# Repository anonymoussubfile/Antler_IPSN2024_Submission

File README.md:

# Antler_IPSN2024_Submission

We upload all our source code and files for reviewer's reference, including hardware design files, algorithm related files, data collection and model inference related projects on Arduino and MSP, our self-collected datasets, and etc.

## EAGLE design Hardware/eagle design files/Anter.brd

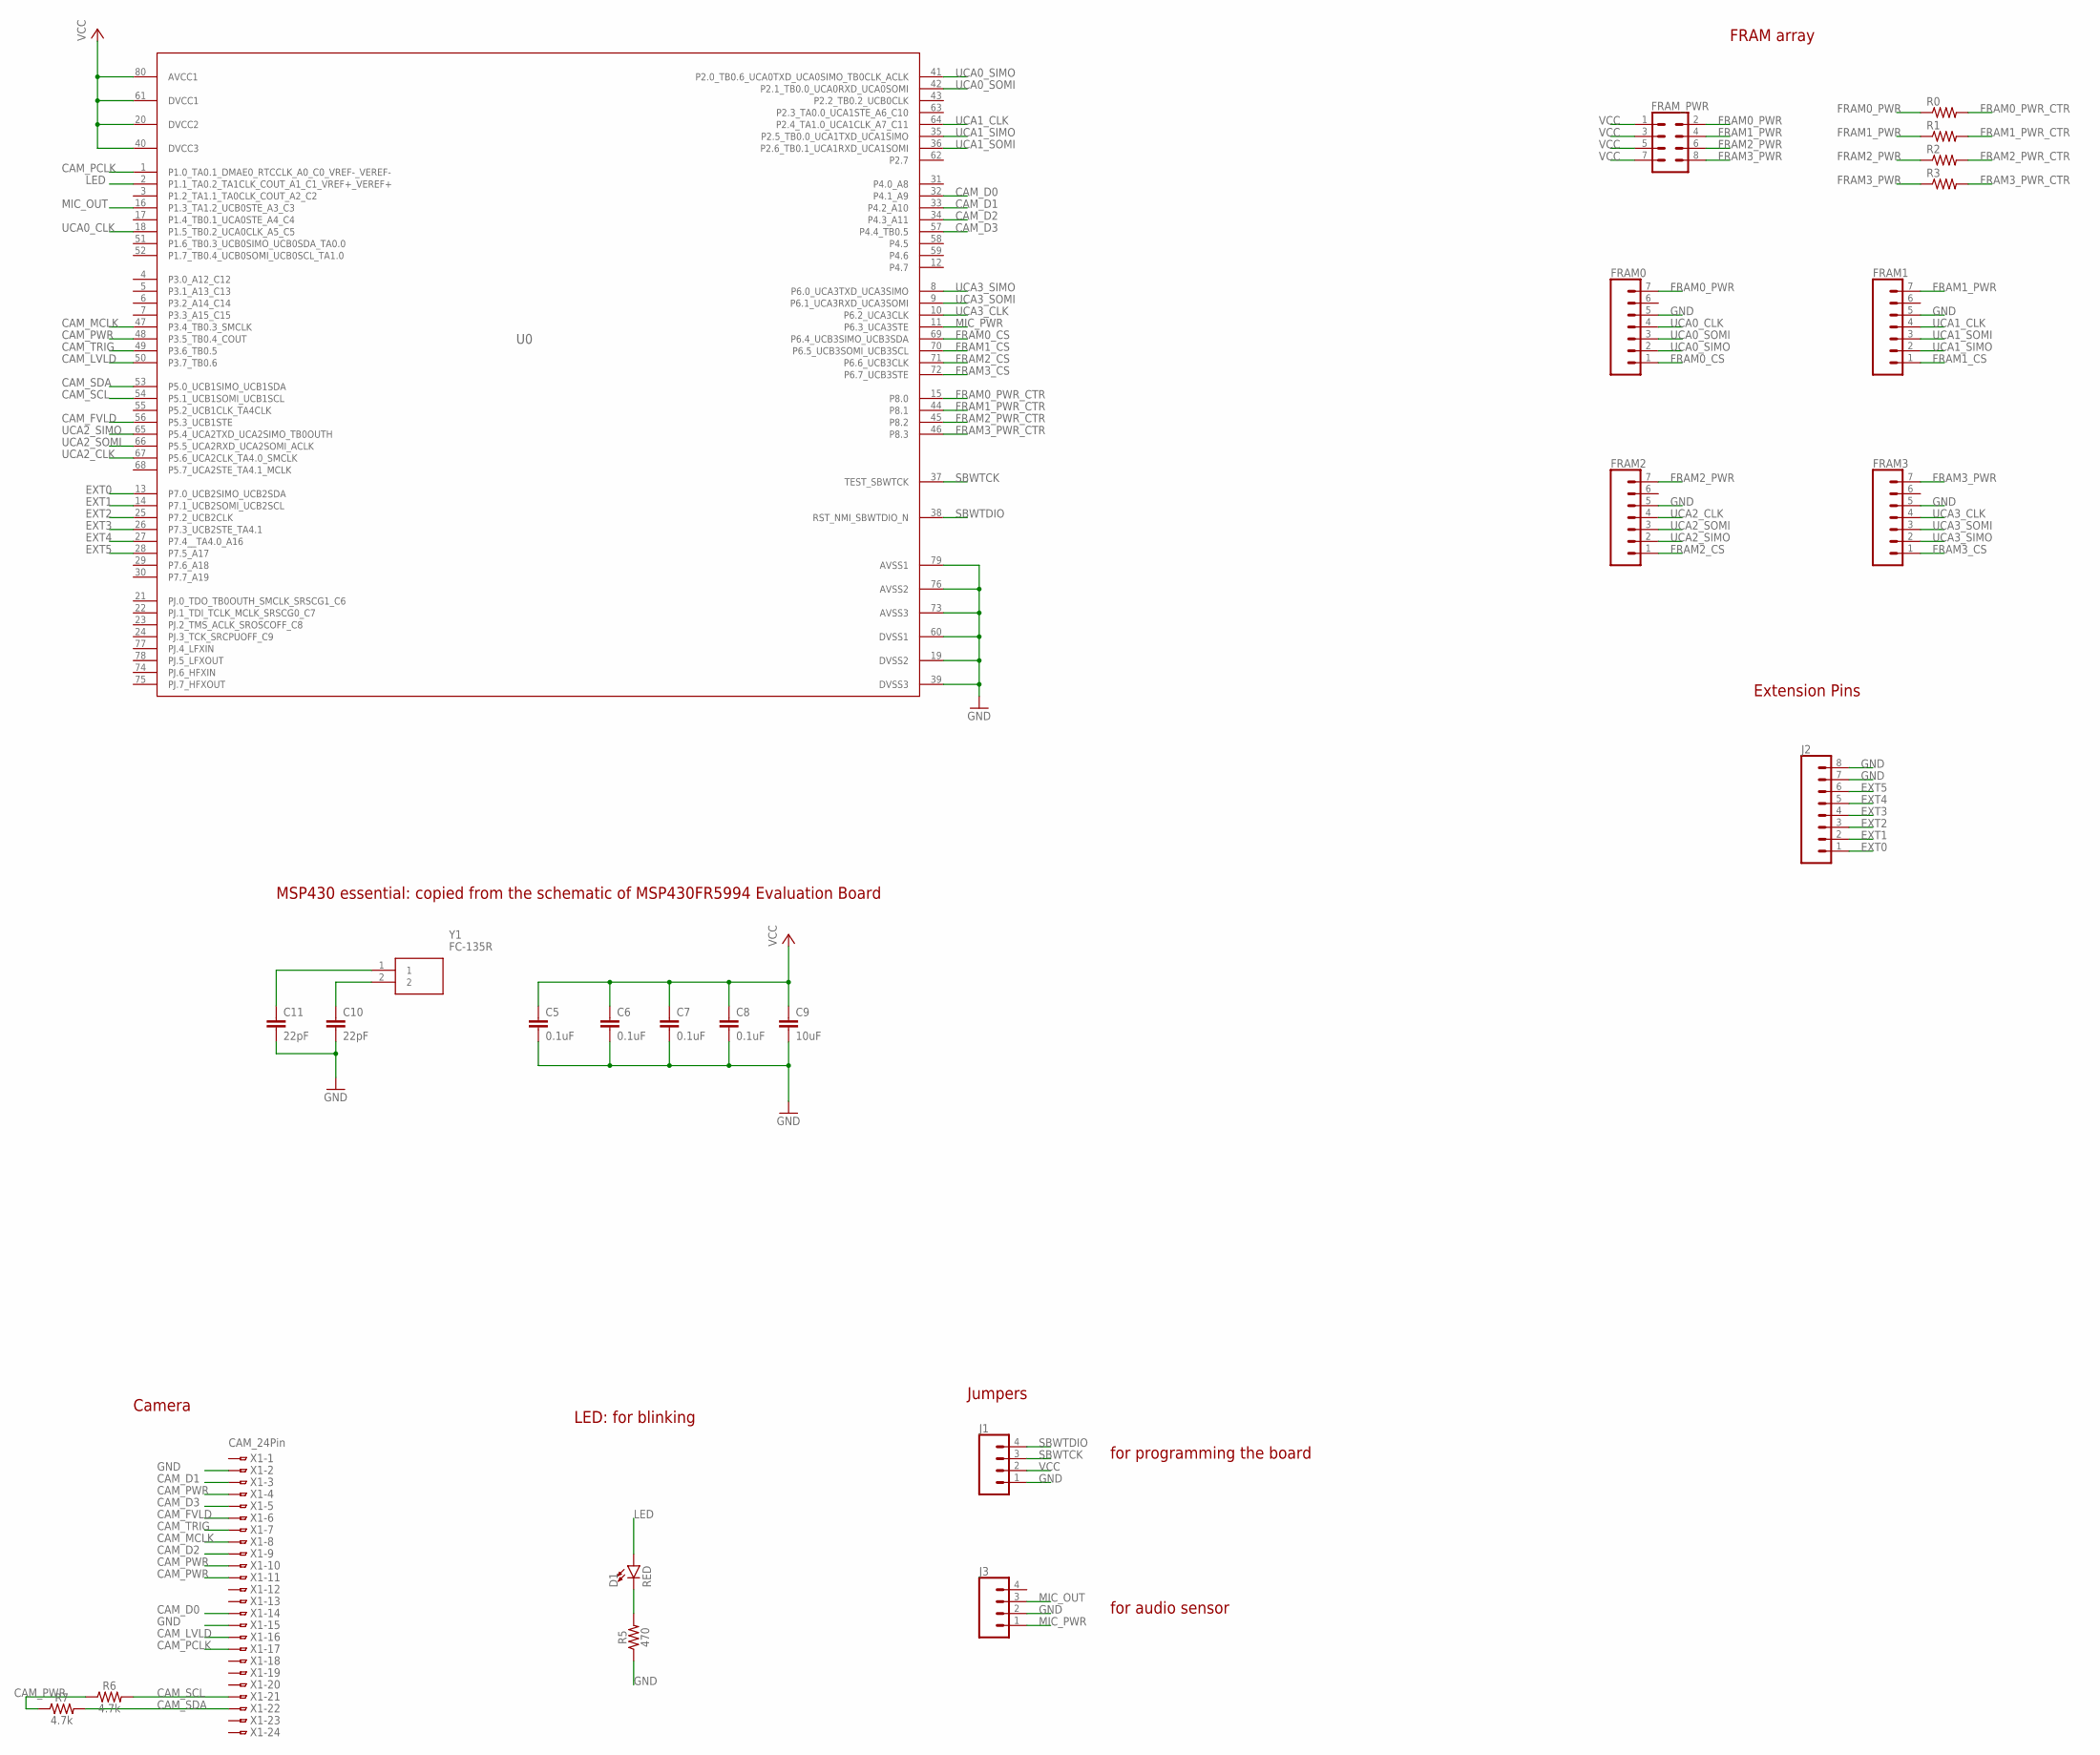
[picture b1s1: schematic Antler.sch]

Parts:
C5, C6, C7, C8: 0.1uF; 0603
C9: 10uF; 0603
C10, C11: 22pF; 0603
D1: RED; LED-0603
FRAM0, FRAM1, FRAM2, FRAM3: CONN_07LOCK; 1X07_LOCK
FRAM_PWR: CONN_04X2; 2X4
J1, J3: CONN_04LOCK; 1X04_LOCK
J2: CONN_08LOCK; 1X08_LOCK
R0, R1, R2, R3: R-US_R0603; R0603
R5: 470; 0603
R6, R7: 4.7k; 0603
U0: MSP430FR5994PN; PN0080A_N
X1: CAM_24Pin; FH12-24S-0.5SH
Y1: FC-135R; FC135327680KAAG0

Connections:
CAM_D0: U0.32 (P4.1_A9), X1.14
CAM_D1: U0.33 (P4.2_A10), X1.3
CAM_D2: U0.34 (P4.3_A11), X1.9
CAM_D3: U0.57 (P4.4_TB0.5), X1.5
CAM_FVLD: U0.56 (P5.3_UCB1STE), X1.6
CAM_LVLD: U0.50 (P3.7_TB0.6), X1.16
CAM_MCLK: U0.47 (P3.4_TB0.3_SMCLK), X1.8
CAM_PCLK: U0.1 (P1.0_TA0.1_DMAE0_RTCCLK_A0_C0_VREF-_VER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), X1.17
CAM_PWR: R6.1, R7.1, U0.48 (P3.5_TB0.4_COUT), X1.4, X1.10, X1.11
CAM_SCL: R6.2, U0.54 (P5.1_UCB1SOMI_UCB1SCL), X1.21
CAM_SDA: R7.2, U0.53 (P5.0_UCB1SIMO_UCB1SDA), X1.22
CAM_TRIG: U0.49 (P3.6_TB0.5), X1.7
EXT0: J2.1, U0.13 (P7.0_UCB2SIMO_UCB2SDA)
EXT1: J2.2, U0.14 (P7.1_UCB2SOMI_UCB2SCL)
EXT2: J2.3, U0.25 (P7.2_UCB2CLK)
EXT3: J2.4, U0.26 (P7.3_UCB2STE_TA4.1)
EXT4: J2.5, U0.27 (P7.4__TA4.0_A16)
EXT5: J2.6, U0.28 (P7.5_A17)
FRAM0_CS: FRAM0.1, U0.69 (P6.4_UCB3SIMO_UCB3SDA)
FRAM0_PWR: FRAM0.7, FRAM_PWR.2, R0.1
FRAM0_PWR_CTR: R0.2, U0.15 (P8.0)
FRAM1_CS: FRAM1.1, U0.70 (P6.5_UCB3SOMI_UCB3SCL)
FRAM1_PWR: FRAM1.7, FRAM_PWR.4, R1.1
FRAM1_PWR_CTR: R1.2, U0.44 (P8.1)
FRAM2_CS: FRAM2.1, U0.71 (P6.6_UCB3CLK)
FRAM2_PWR: FRAM2.7, FRAM_PWR.6, R2.1
FRAM2_PWR_CTR: R2.2, U0.45 (P8.2)
FRAM3_CS: FRAM3.1, U0.72 (P6.7_UCB3STE)
FRAM3_PWR: FRAM3.7, FRAM_PWR.8, R3.1
FRAM3_PWR_CTR: R3.2, U0.46 (P8.3)
GND: C5.2, C6.2, C7.2, C8.2, C9.2, C10.2, C11.2, FRAM0.5, FRAM1.5, FRAM2.5, FRAM3.5, J1.1, J2.7, J2.8, J3.2, R5.1, U0.19 (DVSS2), U0.39 (DVSS3), U0.60 (DVSS1), U0.73 (AVSS3), U0.76 (AVSS2), U0.79 (AVSS1), X1.2, X1.15
LED: D1.A, U0.2 (P1.1_TA0.2_TA1CLK_COUT_A1_C1_VREF+_VERE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)
MIC_OUT: J3.3, U0.16 (P1.3_TA1.2_UCB0STE_A3_C3)
MIC_PWR: J3.1, U0.11 (P6.3_UCA3STE)
unnamed: C10.1, Y1.2
unnamed: C11.1, Y1.1
unnamed: D1.C, R5.2
SBWTCK: J1.3, U0.37 (TEST_SBWTCK)
SBWTDIO: J1.4, U0.38 (RST_NMI_SBWTDIO_N)
UCA0_CLK: FRAM0.4, U0.18 (P1.5_TB0.2_UCA0CLK_A5_C5)
UCA0_SIMO: FRAM0.2, U0.41 (P2.0_TB0.6_UCA0TXD_UCA0SIMO_TB0CLK_ACLK)
UCA0_SOMI: FRAM0.3, U0.42 (P2.1_TB0.0_UCA0RXD_UCA0SOMI)
UCA1_CLK: FRAM1.4, U0.64 (P2.4_TA1.0_UCA1CLK_A7_C11)
UCA1_SIMO: FRAM1.2, U0.35 (P2.5_TB0.0_UCA1TXD_UCA1SIMO)
UCA1_SOMI: FRAM1.3, U0.36 (P2.6_TB0.1_UCA1RXD_UCA1SOMI)
UCA2_CLK: FRAM2.4, U0.67 (P5.6_UCA2CLK_TA4.0_SMCLK)
UCA2_SIMO: FRAM2.2, U0.65 (P5.4_UCA2TXD_UCA2SIMO_TB0OUTH)
UCA2_SOMI: FRAM2.3, U0.66 (P5.5_UCA2RXD_UCA2SOMI_ACLK)
UCA3_CLK: FRAM3.4, U0.10 (P6.2_UCA3CLK)
UCA3_SIMO: FRAM3.2, U0.8 (P6.0_UCA3TXD_UCA3SIMO)
UCA3_SOMI: FRAM3.3, U0.9 (P6.1_UCA3RXD_UCA3SOMI)
VCC: C5.1, C6.1, C7.1, C8.1, C9.1, FRAM_PWR.1, FRAM_PWR.3, FRAM_PWR.5, FRAM_PWR.7, J1.2, U0.20 (DVCC2), U0.40 (DVCC3), U0.61 (DVCC1), U0.80 (AVCC1)

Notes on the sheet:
MSP430 essential: copied from the schematic of MSP430FR5994 Evaluation Board
Camera
LED: for blinking
Jumpers
for programming the board
for audio sensor
FRAM array
Extension Pins

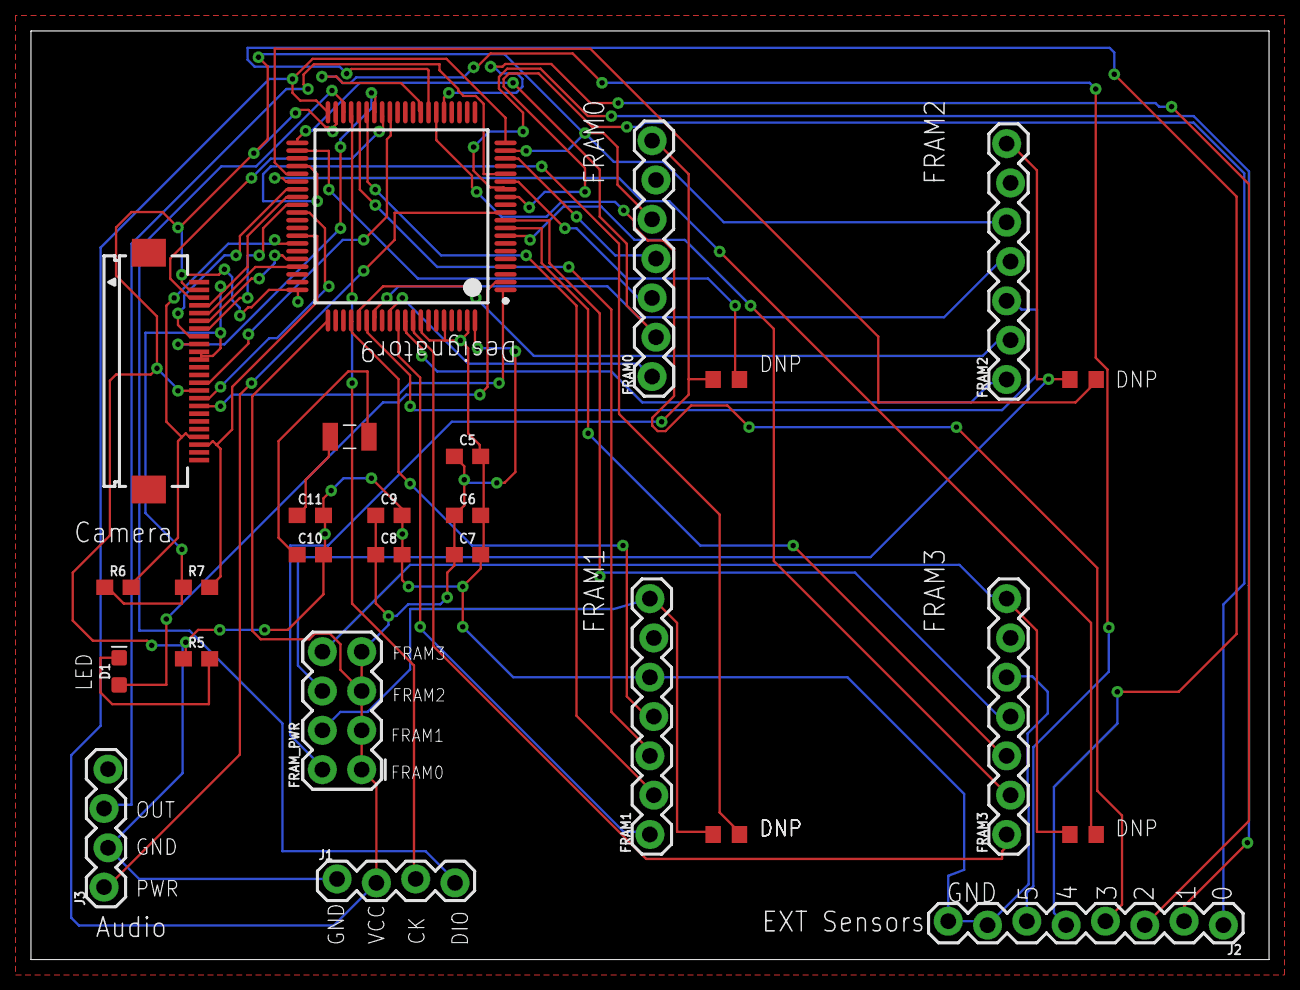
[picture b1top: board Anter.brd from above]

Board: 2 copper layers, 80.0 x 60.0 mm, 26 parts (0 on the bottom side), 52 nets.

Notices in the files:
parts and their libraries:
SparkFun-Capacitors: Licensing: Creative Commons ShareAlike 4.0 International - https://creativecommons.org/licenses/by-sa/4.0
